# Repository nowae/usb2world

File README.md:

# usb2world
A simple boards that convert USB to other protocols

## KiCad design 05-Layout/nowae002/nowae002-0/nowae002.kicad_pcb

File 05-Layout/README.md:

# usb2world

In this folder you can find the boards design files of project.
* NOWAE001 - USB to UART Board

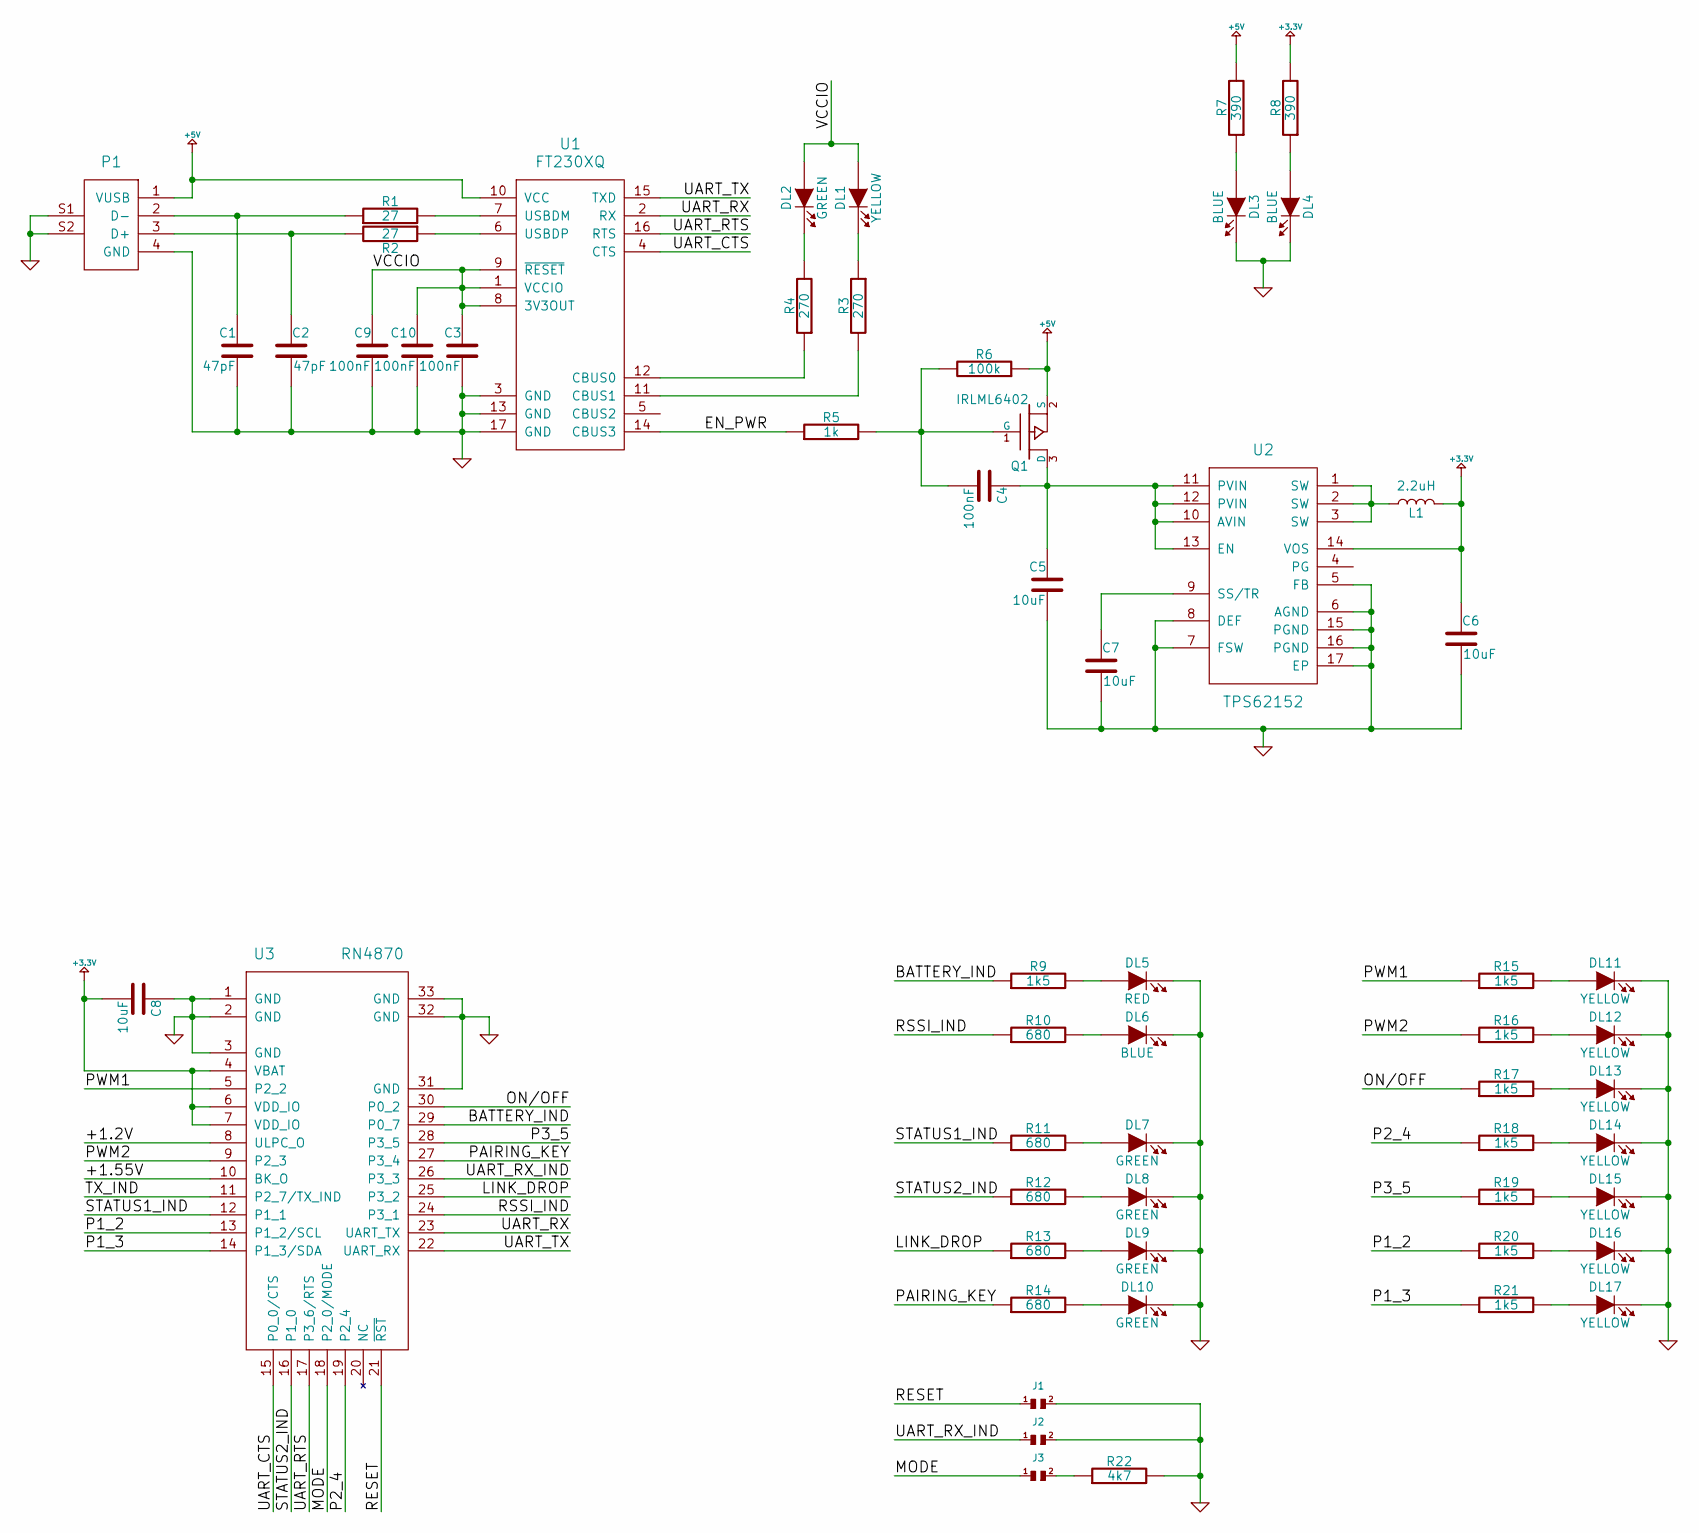
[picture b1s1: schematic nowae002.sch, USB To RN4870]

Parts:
C1, C2: 47pF; CAPACITOR-0402
C3, C4, C9, C10: 100nF; CAPACITOR-0402
C5, C6, C7, C8: 10uF; CAPACITOR-0402
DL1, DL11, DL12, DL13, DL14, DL15, DL16, DL17: YELLOW; LED-0402
DL2, DL7, DL8, DL9, DL10: GREEN; LED-0402
DL3, DL4, DL6: BLUE; LED-0402
DL5: RED; LED-0402
J1, J2, J3: SMALL_JUMPER; JUMPERSMD-2
L1: 2.2uH; INDUCTOR-0805
P1: USB_A_90; USB-A-WURTH-629004113921; Part Number 629004113921
Q1: IRLML6402; SOT23-3; Part Number IRLML6402PBF
R1, R2: 27; RESISTOR-0402
R3, R4: 270; RESISTOR-0402
R5: 1k; RESISTOR-0402
R6: 100k; RESISTOR-0402
R7, R8: 390; RESISTOR-0402
R9, R15, R16, R17, R18, R19, R20, R21: 1k5; RESISTOR-0402
R10, R11, R12, R13, R14: 680; RESISTOR-0402
R22: 4k7; RESISTOR-0402
U1: FT230XQ; QFN16_4x4_0.65_16+1; Part Number FT230XQ
U2: TPS62152; QFN16_3x3_0.5_16+1; Part Number TPS62152RGTT
U3: RN4870; RN4870U; Part Number RN4870-V/RM118

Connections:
+3.3V: C6.1, C8.2, L1.2, R8.2, U2.14 (VOS), U3.4 (VBAT), U3.6 (VDD_IO), U3.7 (VDD_IO)
+5V: P1.1 (VUSB), Q1.2 (S), R6.1, R7.2, U1.10 (VCC)
/+1.2V: U3.8 (ULPC_O)
/+1.55V: U3.10 (BK_O)
/BATTERY_IND: R9.1, U3.29 (P0_7)
/EN_PWR: R5.1, U1.14 (CBUS3)
/LINK_DROP: R13.1, U3.25 (P3_2)
/MODE: J3.1, U3.18 (P2_0/MODE)
/ON/OFF: R17.1, U3.30 (P0_2)
/P1_2: R20.1, U3.13 (P1_2/SCL)
/P1_3: R21.1, U3.14 (P1_3/SDA)
/P2_4: R18.1, U3.19 (P2_4)
/P3_5: R19.1, U3.28 (P3_5)
/PAIRING_KEY: R14.1, U3.27 (P3_4)
/PWM1: R15.1, U3.5 (P2_2)
/PWM2: R16.1, U3.9 (P2_3)
/RESET: J1.1, U3.21 (~RST)
/RSSI_IND: R10.1, U3.24 (P3_1)
/STATUS1_IND: R11.1, U3.12 (P1_1)
/STATUS2_IND: R12.1, U3.16 (P1_0)
/TX_IND: U3.11 (P2_7/TX_IND)
/UART_CTS: U1.4 (CTS), U3.15 (P0_0/CTS)
/UART_RTS: U1.16 (RTS), U3.17 (P3_6/RTS)
/UART_RX: U1.2 (RX), U3.23 (UART_TX)
/UART_RX_IND: J2.1, U3.26 (P3_3)
/UART_TX: U1.15 (TXD), U3.22 (UART_RX)
/VCCIO: C3.1, C9.1, C10.1, DL1.1 (A), DL2.1 (A), U1.1 (VCCIO), U1.8 (3V3OUT), U1.9 (~RESET)
GND: C1.2, C2.2, C3.2, C5.2, C6.2, C7.2, C8.1, C9.2, C10.2, DL3.2 (K), DL4.2 (K), DL5.2 (K), DL6.2 (K), DL7.2 (K), DL8.2 (K), DL9.2 (K), DL10.2 (K), DL11.2 (K), DL12.2 (K), DL13.2 (K), DL14.2 (K), DL15.2 (K), DL16.2 (K), DL17.2 (K), J1.2, J2.2, P1.4 (GND), P1.S1, P1.S2, R22.2, U1.3 (GND), U1.13 (GND), U1.17 (GND), U2.5 (FB), U2.6 (AGND), U2.7 (FSW), U2.8 (DEF), U2.15 (PGND), U2.16 (PGND), U2.17 (EP), U3.1 (GND), U3.2 (GND), U3.3 (GND), U3.31 (GND), U3.32 (GND), U3.33 (GND)
unnamed: C1.1, P1.2 (D-), R1.1
unnamed: C2.1, P1.3 (D+), R2.2
unnamed: C4.1, C5.1, Q1.3 (D), U2.10 (AVIN), U2.11 (PVIN), U2.12 (PVIN), U2.13 (EN)
unnamed: C4.2, Q1.1 (G), R5.2, R6.2
unnamed: C7.1, U2.9 (SS/TR)
unnamed: DL1.2 (K), R3.1
unnamed: DL2.2 (K), R4.2
unnamed: DL3.1 (A), R7.1
unnamed: DL4.1 (A), R8.1
unnamed: DL5.1 (A), R9.2
unnamed: DL6.1 (A), R10.2
unnamed: DL7.1 (A), R11.2
unnamed: DL8.1 (A), R12.2
unnamed: DL9.1 (A), R13.2
unnamed: DL10.1 (A), R14.2
unnamed: DL11.1 (A), R15.2
unnamed: DL12.1 (A), R16.2
unnamed: DL13.1 (A), R17.2
unnamed: DL14.1 (A), R18.2
unnamed: DL15.1 (A), R19.2
unnamed: DL16.1 (A), R20.2
unnamed: DL17.1 (A), R21.2
unnamed: J3.2, R22.1
unnamed: L1.1, U2.1 (SW), U2.2 (SW), U2.3 (SW)
unnamed: R1.2, U1.7 (USBDM)
unnamed: R2.1, U1.6 (USBDP)
unnamed: R3.2, U1.11 (CBUS1)
unnamed: R4.1, U1.12 (CBUS0)

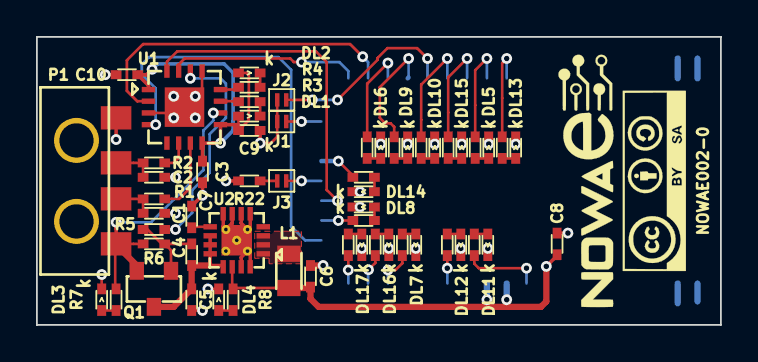
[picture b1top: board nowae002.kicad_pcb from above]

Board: 2 copper layers, 38.0 x 16.0 mm, 58 parts (1 on the bottom side), 53 nets.

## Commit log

2017-02-04 Added project structure
2017-02-04 Added kicad library as submodule
2017-02-06 Removed libkicad sub-module
2017-02-06 Configured library path for schematic and pcb editor
2017-02-09 Configured path for worksheet
2017-02-10 Added schematic file
2017-02-10 Added main circuit
2017-02-10 Added library cache
2017-02-12 Added switching regulator +3.3V
2017-02-12 Added UART output connector
2017-02-12 Added usb plug
2017-02-12 Added led for power supply
2017-02-12 Updated cache lib
2017-02-12 Created nowae002-0 project and designed basic circuit in schematic editor
2017-02-25 Added Vin capacitor on TPS62743 and annotate components
2017-03-06 Added CONNECTOR_MKDS in library table for pcb editor in nowae001
2017-03-06 Changed switching regulator (TPS62743 -> TPS62152) in nowae001
2017-03-06 Added nowae001 board
2017-03-22 Changed output connector in nowae001
2017-04-05 Added leds for bluetooth module signals
2017-04-07 Defined led resistors in nowae002
2017-04-10 Annotated components in nowae002
2017-04-10 Created net file in nowae002
2017-04-10 Updated net file of nowae002
2017-04-10 Modified ref des in nowae002 (U3 -> U1)
2017-04-13 Updated cache.lib in nowae002
2017-04-13 Updated pcb in nowae001
2017-04-13 Updated components association in nowae001
2017-04-13 Updated worksheet in nowae001
2017-04-15 Added logos in nowae001
2017-04-15 Added schematic (pdf) of nowae001
2017-04-15 Moved nowae001 schematic in new folder (07-Production/01-Schematic)
2017-04-15 Updated worksheet in nowae001.kicad_pcb
2017-04-15 Moved nowae001 schematic in new folder (07-Production/01-Schematics/nowae001/nowae001-0)
2017-04-15 Added nowae001-0 gerber files in 07-Production/02-Gerber/nowae001/nowae001-0_2017-04-15
2017-04-23 Added jumper for setting mode (RN4870) in nowae002
2017-04-25 Minor fixes (nowae002)
2017-04-25 Updated nowae002.pro
2017-04-28 Added LOGO.pretty in fp-lib-table for nowae001
2017-04-28 Removed nowae002 project
2017-04-28 Added nowae002 project
2017-05-30 Updated logos and license silkscreen
2017-05-30 Updated gerber files
2018-04-18 Changed P1 footprint and updated net file (nowae002-0)
2018-04-18 WiP: placement components (nowae002-0)
2018-04-18 Updated P1 informations (nowae002-0)
2018-04-18 WiP: placement wires (nowae002-0)
2018-04-18 Changed CBUS pins (nowae002-0) Minor fix (nowae002-0)
2018-04-18 Removed nowae002-cache.lib (nowae002-0)
2018-04-18 Updated fp-lib-table (nowae002-0)
2018-04-18 Added logos. (nowae002-0) Updated U3 footprint. (nowae002-0)
2018-05-24 Updated worksheet (nowae002-0)
2018-11-07 Added project (nowae020-0)
2019-02-06 WiP: schematic (nowae020-0)
2019-02-06 Removed nowae020-cache.lib (nowae020.0)
2019-02-06 Added sym-lib-table (nowae020-0)
